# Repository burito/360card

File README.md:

# 360card

This is a simple board to make it easier for me to hook up random pots and buttons to an Arduino Pro Micro so it can act as an Xbox360 controller. I made it in KiCad.

## board-test
This is a simple Arduino Sketch that will read all the pins and output everything over the serial interface. Good for testing the connections, and finding out the values returned by your pots before you reflash it with the 360 firmware.

## 360
This firmware to use is this one...
https://github.com/bootsector/XInputPadMicro
...but it's GPLv3...

On Mac you'll need...

* Install [CrossPack-AVR-20131216.dmg](https://www.obdev.at/products/crosspack/download.html)
* If you head [here](http://extremeelectronics.co.in/avr-tutorials/using-adc-of-avr-microcontroller/) you will find an explanation on how to read the ADC's in the avr-gcc environment.
* in this land, the digital pins are named like PD4, PC6, PB4, etc.
* Also, the Analogue pins are named ADC4 and the like.
* After flashing the 360 firmware, it won't show up to the flashing tools, unless you short Reset with Ground twice in rapid succession. That's what the button is for.

```
void adc_init()
{
    // AREF = AVcc
    ADMUX = (1<<REFS0);
 
    // ADC Enable and prescaler of 128
    // 16000000/128 = 125000
    ADCSRA = (1<<ADEN)|(1<<ADPS2)|(1<<ADPS1)|(1<<ADPS0);
}

uint16_t adc_read(uint8_t ch)
{
  // select the corresponding channel 0~7
  // ANDing with ’7′ will always keep the value
  // of ‘ch’ between 0 and 7
  ch &= 0b00000111;  // AND operation with 7
  ADMUX = (ADMUX & 0xF8)|ch; // clears the bottom 3 bits before ORing
 
  // start single convertion
  // write ’1′ to ADSC
  ADCSRA |= (1<<ADSC);
 
  // wait for conversion to complete
  // ADSC becomes ’0′ again
  // till then, run loop continuously
  while(ADCSRA & (1<<ADSC));
 
  return (ADC);
}
```

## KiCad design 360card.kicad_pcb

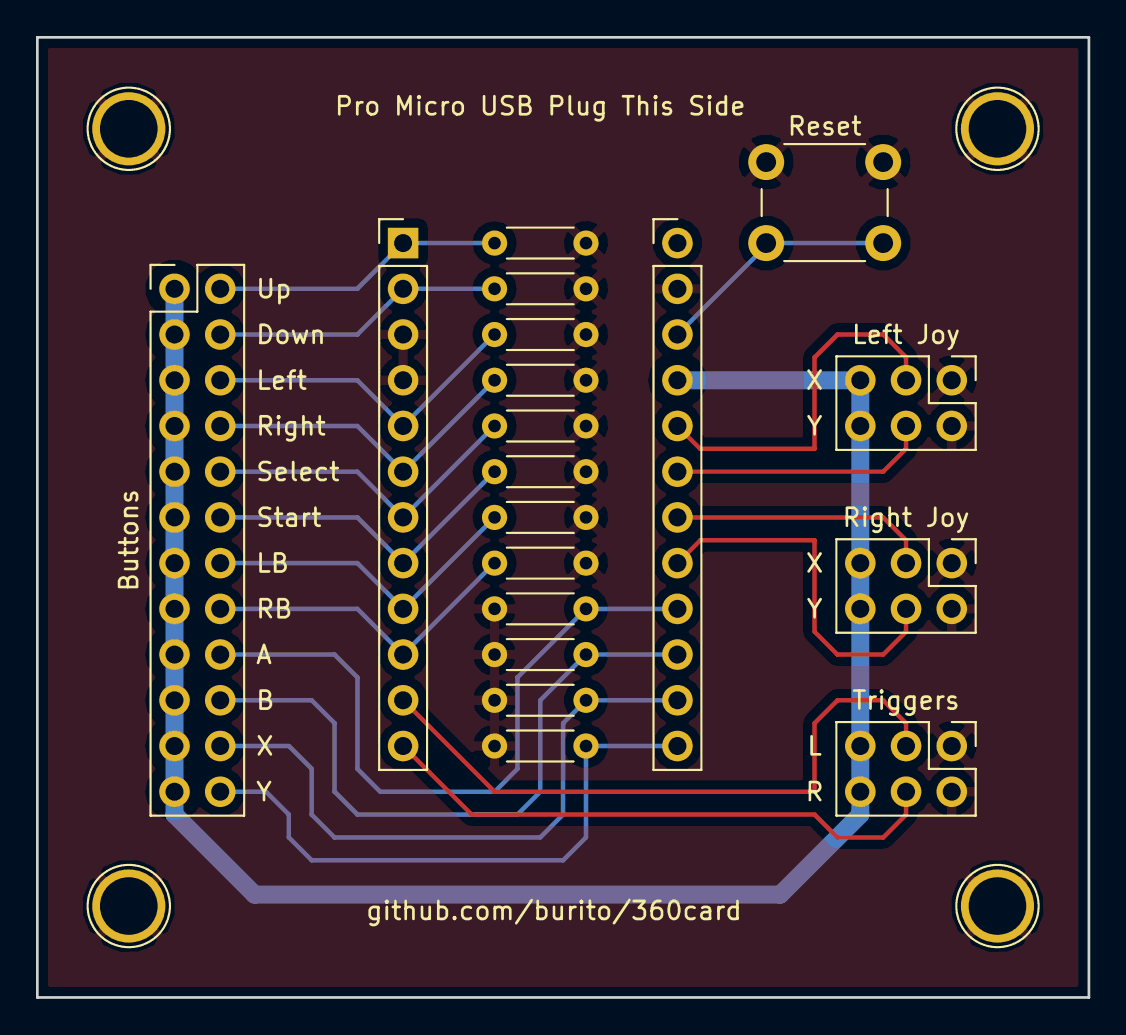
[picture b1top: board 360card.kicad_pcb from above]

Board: 2 copper layers, 58.4 x 53.3 mm, 19 parts (0 on the bottom side), 21 nets.

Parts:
Buttons: Buttons; Pin_Header_Straight_2x12_Pitch2.54mm
J2, J3: Conn_01x12_Female; Socket_Strip_Straight_1x12_Pitch2.54mm
Left Joy: Left Joystick; Pin_Header_Straight_2x03_Pitch2.54mm
R1, R2, R3, R4, R5, R6, R7, R8, R9, R10, R11, R12: 10k; R_Axial_DIN0204_L3.6mm_D1.6mm_P5.08mm_Horizontal
Reset: Reset; SW_PUSH_6mm
Right Joy: Right Joystick; Pin_Header_Straight_2x03_Pitch2.54mm
Triggers: Triggers; Pin_Header_Straight_2x03_Pitch2.54mm

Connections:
/+5V: Buttons.1, Buttons.3, Buttons.5, Buttons.7, Buttons.9, Buttons.11, Buttons.13, Buttons.15, Buttons.17, Buttons.19, Buttons.21, Buttons.23, J3.4, Left Joy.5, Left Joy.6, Right Joy.5, Right Joy.6, Triggers.5, Triggers.6
/GND: J2.3, J2.4, J3.2, Left Joy.1, Left Joy.2, R1.1, R2.1, R3.1, R4.1, R5.1, R6.1, R7.1, R8.1, R9.2, R10.2, R11.2, R12.2, Reset.1, Right Joy.2, Right Joy.e1, Triggers.1, Triggers.2
/Reset: J3.3, Reset.2
unnamed: Buttons.2, J2.1, R1.2
unnamed: Buttons.4, J2.2, R2.2
unnamed: Buttons.6, J2.5, R3.2
unnamed: Buttons.8, J2.6, R4.2
unnamed: Buttons.10, J2.7, R5.2
unnamed: Buttons.12, J2.8, R6.2
unnamed: Buttons.14, J2.9, R7.2
unnamed: Buttons.16, J2.10, R8.2
unnamed: Buttons.18, J3.9, R9.1
unnamed: Buttons.20, J3.10, R10.1
unnamed: Buttons.22, J3.11, R11.1
unnamed: Buttons.24, J3.12, R12.1
unnamed: J2.11, Triggers.3
unnamed: J2.12, Triggers.4
unnamed: J3.5, Left Joy.3
unnamed: J3.6, Left Joy.4
unnamed: J3.7, Right Joy.3
unnamed: J3.8, Right Joy.4

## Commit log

2018-02-09 Wrote some documentation, added the arduino test
2018-04-02 Reworked the PCB design
